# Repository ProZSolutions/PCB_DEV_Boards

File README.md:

# PCB_DEV_Boards
12 Volt IR sensor with Relay Board 
https://github.com/ProZSolutions/PCB_DEV_Boards/tree/main/Power_supply_with_sensor_board
Kicad

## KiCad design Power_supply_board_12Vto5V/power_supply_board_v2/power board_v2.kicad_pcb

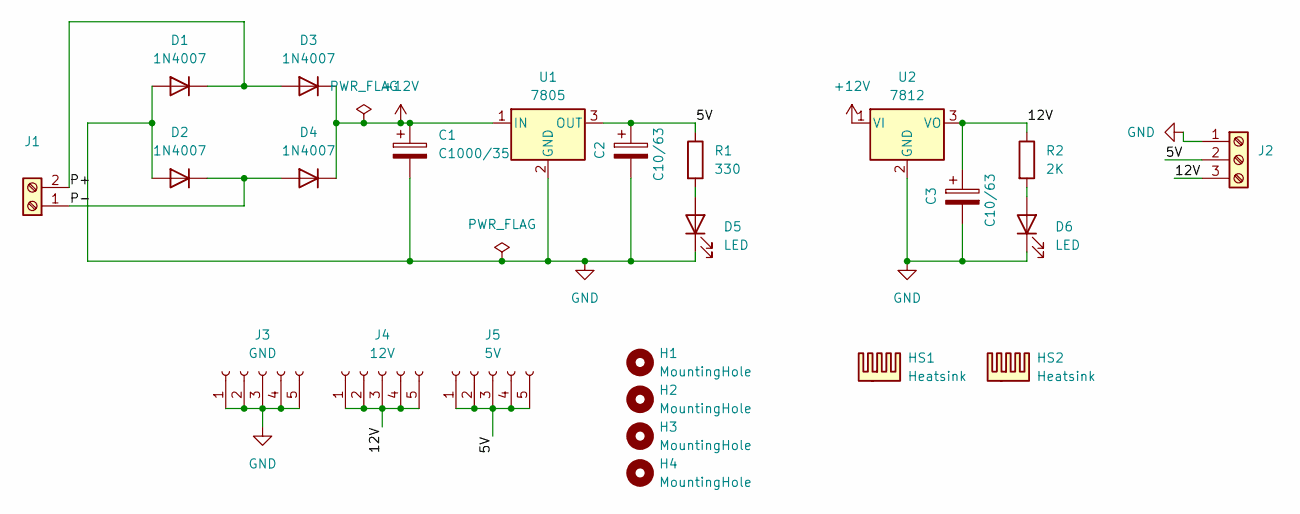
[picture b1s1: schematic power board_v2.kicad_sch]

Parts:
C1: C1000/35; CP_Radial_D10.0mm_P5.00mm
C2, C3: C10/63; CP_Radial_D5.0mm_P2.50mm
D1, D2, D3, D4: 1N4007; D_DO-41_SOD81_P10.16mm_Horizontal
D5, D6: LED; LED_D3.0mm_FlatTop
H1, H2, H3, H4: MountingHole; MountingHole_3.5mm
HS1, HS2: Heatsink; HeatSink_PI49_TO220_20mm
J1: Screw_Terminal_01x02; TerminalBlock_Phoenix_MKDS-1,5-2_1x02_P5.00mm_Horizontal
J2: Screw_Terminal_01x03; TerminalBlock_Phoenix_MKDS-1,5-3_1x03_P5.00mm_Horizontal
J3: GND; PinHeader_1x05_P2.54mm_Vertical
J4: 12V; PinHeader_1x05_P2.54mm_Vertical
J5: 5V; PinHeader_1x05_P2.54mm_Vertical
R1: 330; R_Axial_DIN0207_L6.3mm_D2.5mm_P10.16mm_Horizontal
R2: 2K; R_Axial_DIN0207_L6.3mm_D2.5mm_P10.16mm_Horizontal
U1: 7805; TO-220-3_Vertical
U2: 7812; TO-220-3_Vertical

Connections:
+12V: C1.1, D3.1 (K), D4.1 (K), U1.1 (IN), U2.1 (VI)
/5V: C2.1, J2.2, J5.1, J5.2, J5.3, J5.4, J5.5, R1.1, U1.3 (OUT)
/12V: C3.1, J2.3, J4.1, J4.2, J4.3, J4.4, J4.5, R2.1, U2.3 (VO)
/P+: D1.1 (K), D3.2 (A), J1.2
/P-: D2.1 (K), D4.2 (A), J1.1
GND: C1.2, C2.2, C3.2, D1.2 (A), D2.2 (A), D5.1 (K), D6.1 (K), J2.1, J3.1, J3.2, J3.3, J3.4, J3.5, U1.2 (GND), U2.2 (GND)
unnamed: D5.2 (A), R1.2
unnamed: D6.2 (A), R2.2

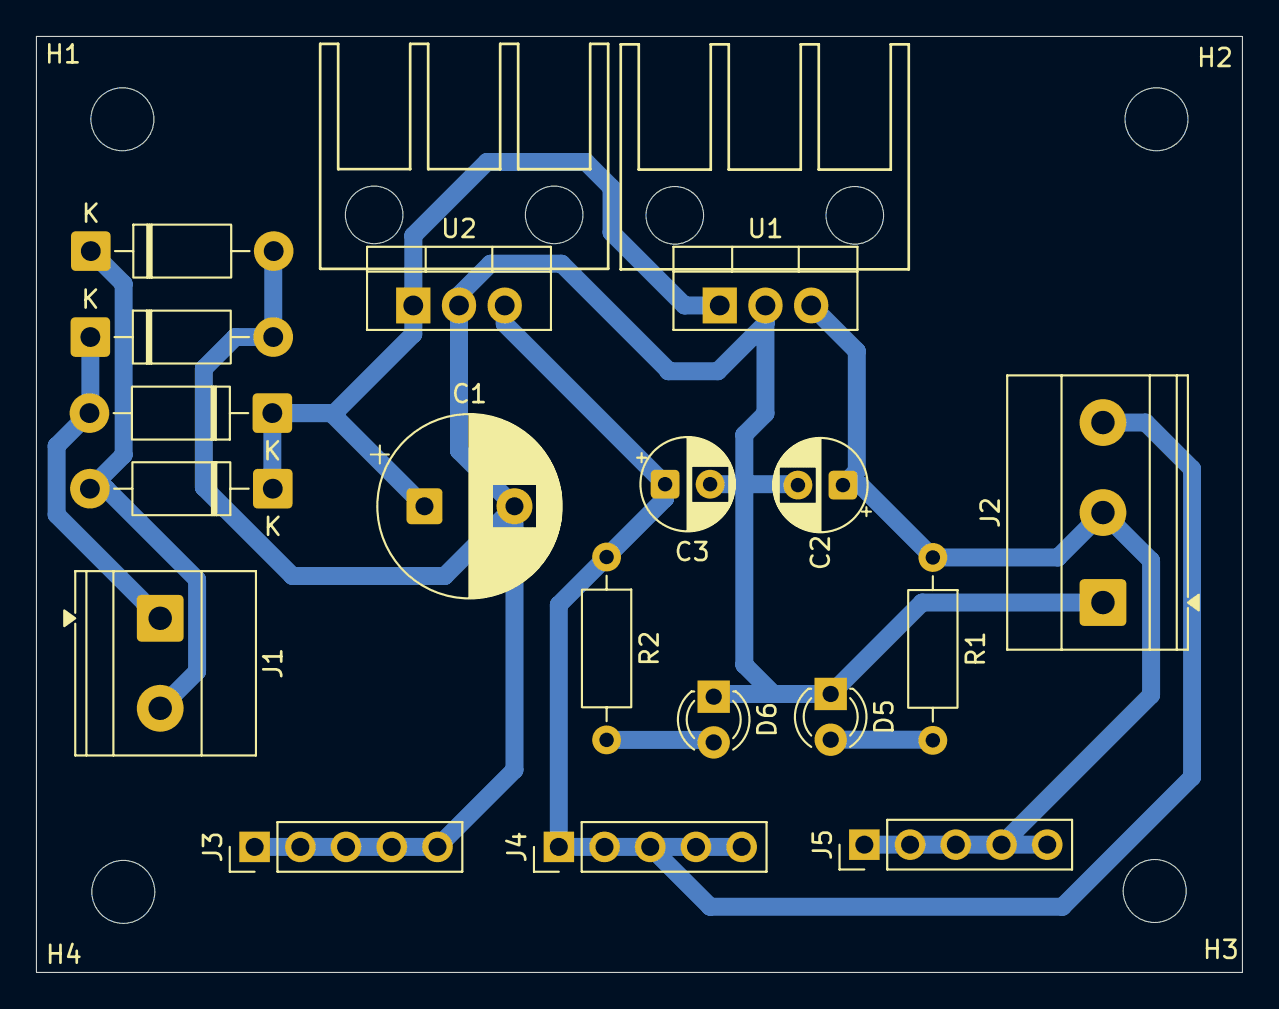
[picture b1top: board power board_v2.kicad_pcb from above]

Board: 2 copper layers, 67.0 x 52.0 mm, 24 parts (0 on the bottom side), 8 nets.

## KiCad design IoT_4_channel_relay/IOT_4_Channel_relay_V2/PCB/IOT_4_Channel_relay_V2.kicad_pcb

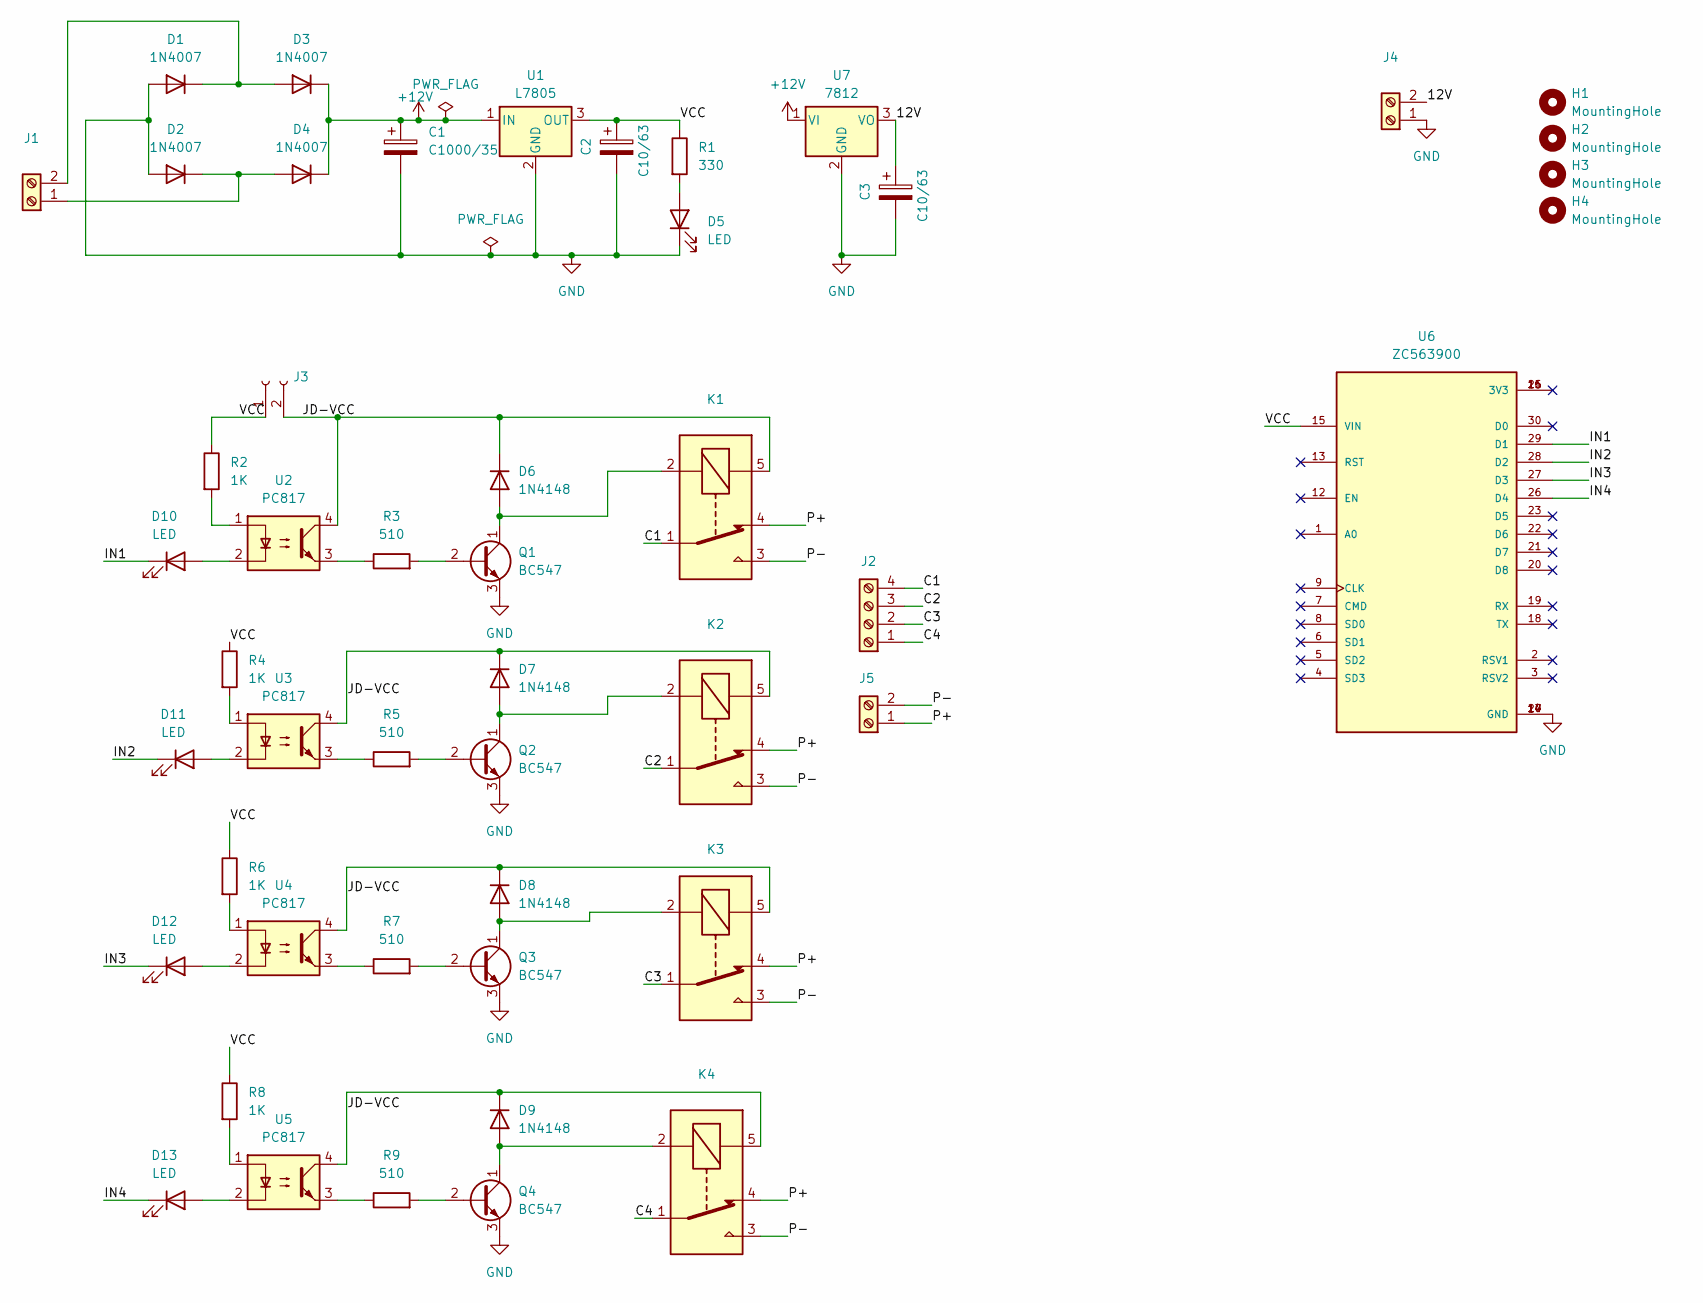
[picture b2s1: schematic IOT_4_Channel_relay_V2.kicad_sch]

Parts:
C1: C1000/35; CP_Radial_D10.0mm_P5.00mm
C2, C3: C10/63; CP_Radial_D5.0mm_P2.50mm
D1, D2, D3, D4: 1N4007; D_DO-41_SOD81_P10.16mm_Horizontal
D5, D10, D11, D12, D13: LED; LED_D3.0mm_FlatTop
D6, D7, D8, D9: 1N4148; D_DO-35_SOD27_P7.62mm_Horizontal
H1, H2, H3, H4: MountingHole; MountingHole_3.5mm
J1, J5: Screw_Terminal_01x02; TerminalBlock_Phoenix_MKDS-1,5-2_1x02_P5.00mm_Horizontal
J2: Screw_Terminal_01x04; TerminalBlock_Phoenix_MKDS-1,5-4-5.08_1x04_P5.08mm_Horizont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
J3: Conn_01x02_Socket; PinHeader_1x02_P2.54mm_Vertical
J4: Screw_Terminal_01x02; PinHeader_1x02_P2.54mm_Vertical
K1, K2, K3, K4: SANYOU_SRD_Form_C; Relay_SPDT_SANYOU_SRD_Series_Form_C
Q1, Q2, Q3, Q4: BC547; TO-92_Wide
R1: 330; R_Axial_DIN0207_L6.3mm_D2.5mm_P10.16mm_Horizontal
R2, R4, R6, R8: 1K; R_Axial_DIN0207_L6.3mm_D2.5mm_P10.16mm_Horizontal
R3, R5, R7, R9: 510; R_Axial_DIN0207_L6.3mm_D2.5mm_P10.16mm_Horizontal
U1: L7805; TO-220-3_Vertical
U2, U3, U4, U5: PC817; DIP-4_W7.62mm
U6: ZC563900; MODULE_ZC563900; PARTREV 1.0
U7: 7812; TO-220-3_Vertical

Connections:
+12V: C1.1, D3.1 (K), D4.1 (K), U1.1 (IN), U7.1 (VI)
/12V: C3.1, J4.2, U7.3 (VO)
/C1: J2.4, K1.1
/C2: J2.3, K2.1
/C3: J2.2, K3.1
/C4: J2.1, K4.1
/IN1: D10.1 (K), U6.29 (D1)
/IN2: D11.1 (K), U6.28 (D2)
/IN3: D12.1 (K), U6.27 (D3)
/IN4: D13.1 (K), U6.26 (D4)
/JD-VCC: D6.1 (K), D7.1 (K), D8.1 (K), D9.1 (K), J3.2, K1.5, K2.5, K3.5, K4.5, U2.4, U3.4, U4.4, U5.4
/P+: J5.1, K1.4, K2.4, K3.4, K4.4
/P-: J5.2, K1.3, K2.3, K3.3, K4.3
/VCC: C2.1, J3.1, R1.1, R2.1, R4.1, R6.1, R8.1, U1.3 (OUT), U6.15 (VIN)
GND: C1.2, C2.2, C3.2, D1.2 (A), D2.2 (A), D5.1 (K), J4.1, Q1.3 (E), Q2.3 (E), Q3.3 (E), Q4.3 (E), U1.2 (GND), U6.10 (GND), U6.14 (GND), U6.17 (GND), U6.24 (GND), U7.2 (GND)
unnamed: D1.1 (K), D3.2 (A), J1.2
unnamed: D2.1 (K), D4.2 (A), J1.1
unnamed: D5.2 (A), R1.2
unnamed: D6.2 (A), K1.2, Q1.1 (C)
unnamed: D7.2 (A), K2.2, Q2.1 (C)
unnamed: D8.2 (A), K3.2, Q3.1 (C)
unnamed: D9.2 (A), K4.2, Q4.1 (C)
unnamed: D10.2 (A), U2.2
unnamed: D11.2 (A), U3.2
unnamed: D12.2 (A), U4.2
unnamed: D13.2 (A), U5.2
unnamed: Q1.2 (B), R3.2
unnamed: Q2.2 (B), R5.2
unnamed: Q3.2 (B), R7.2
unnamed: Q4.2 (B), R9.2
unnamed: R2.2, U2.1
unnamed: R3.1, U2.3
unnamed: R4.2, U3.1
unnamed: R5.1, U3.3
unnamed: R6.2, U4.1
unnamed: R7.1, U4.3
unnamed: R8.2, U5.1
unnamed: R9.1, U5.3

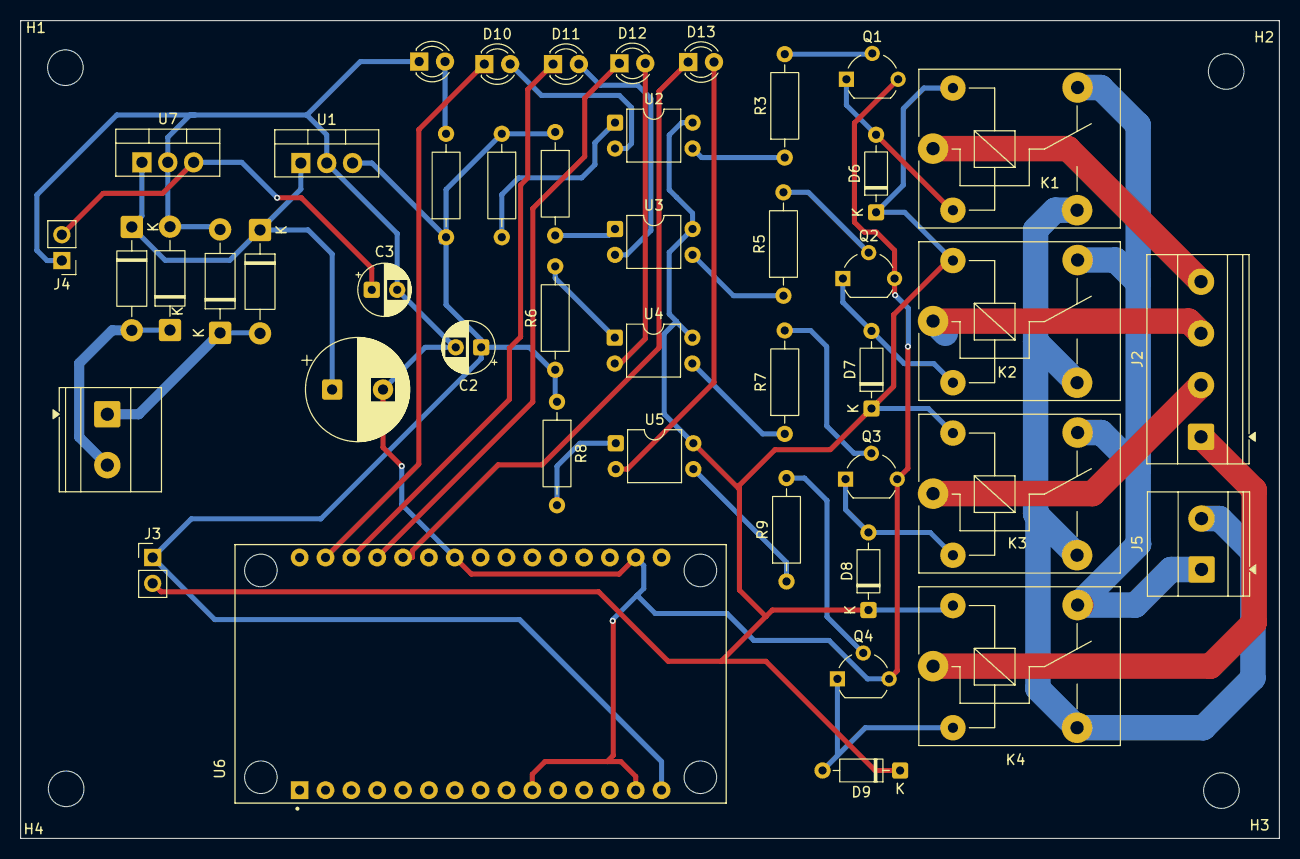
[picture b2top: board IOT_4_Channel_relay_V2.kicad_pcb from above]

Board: 2 copper layers, 123.7 x 80.3 mm, 49 parts (0 on the bottom side), 38 nets.

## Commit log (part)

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2024-07-20 Power_supply_with_sensor_based_Relay_controll_board_v1 initial update.
2024-07-22 Power_supply_with_sensor_board
2025-11-11 iot and power board
